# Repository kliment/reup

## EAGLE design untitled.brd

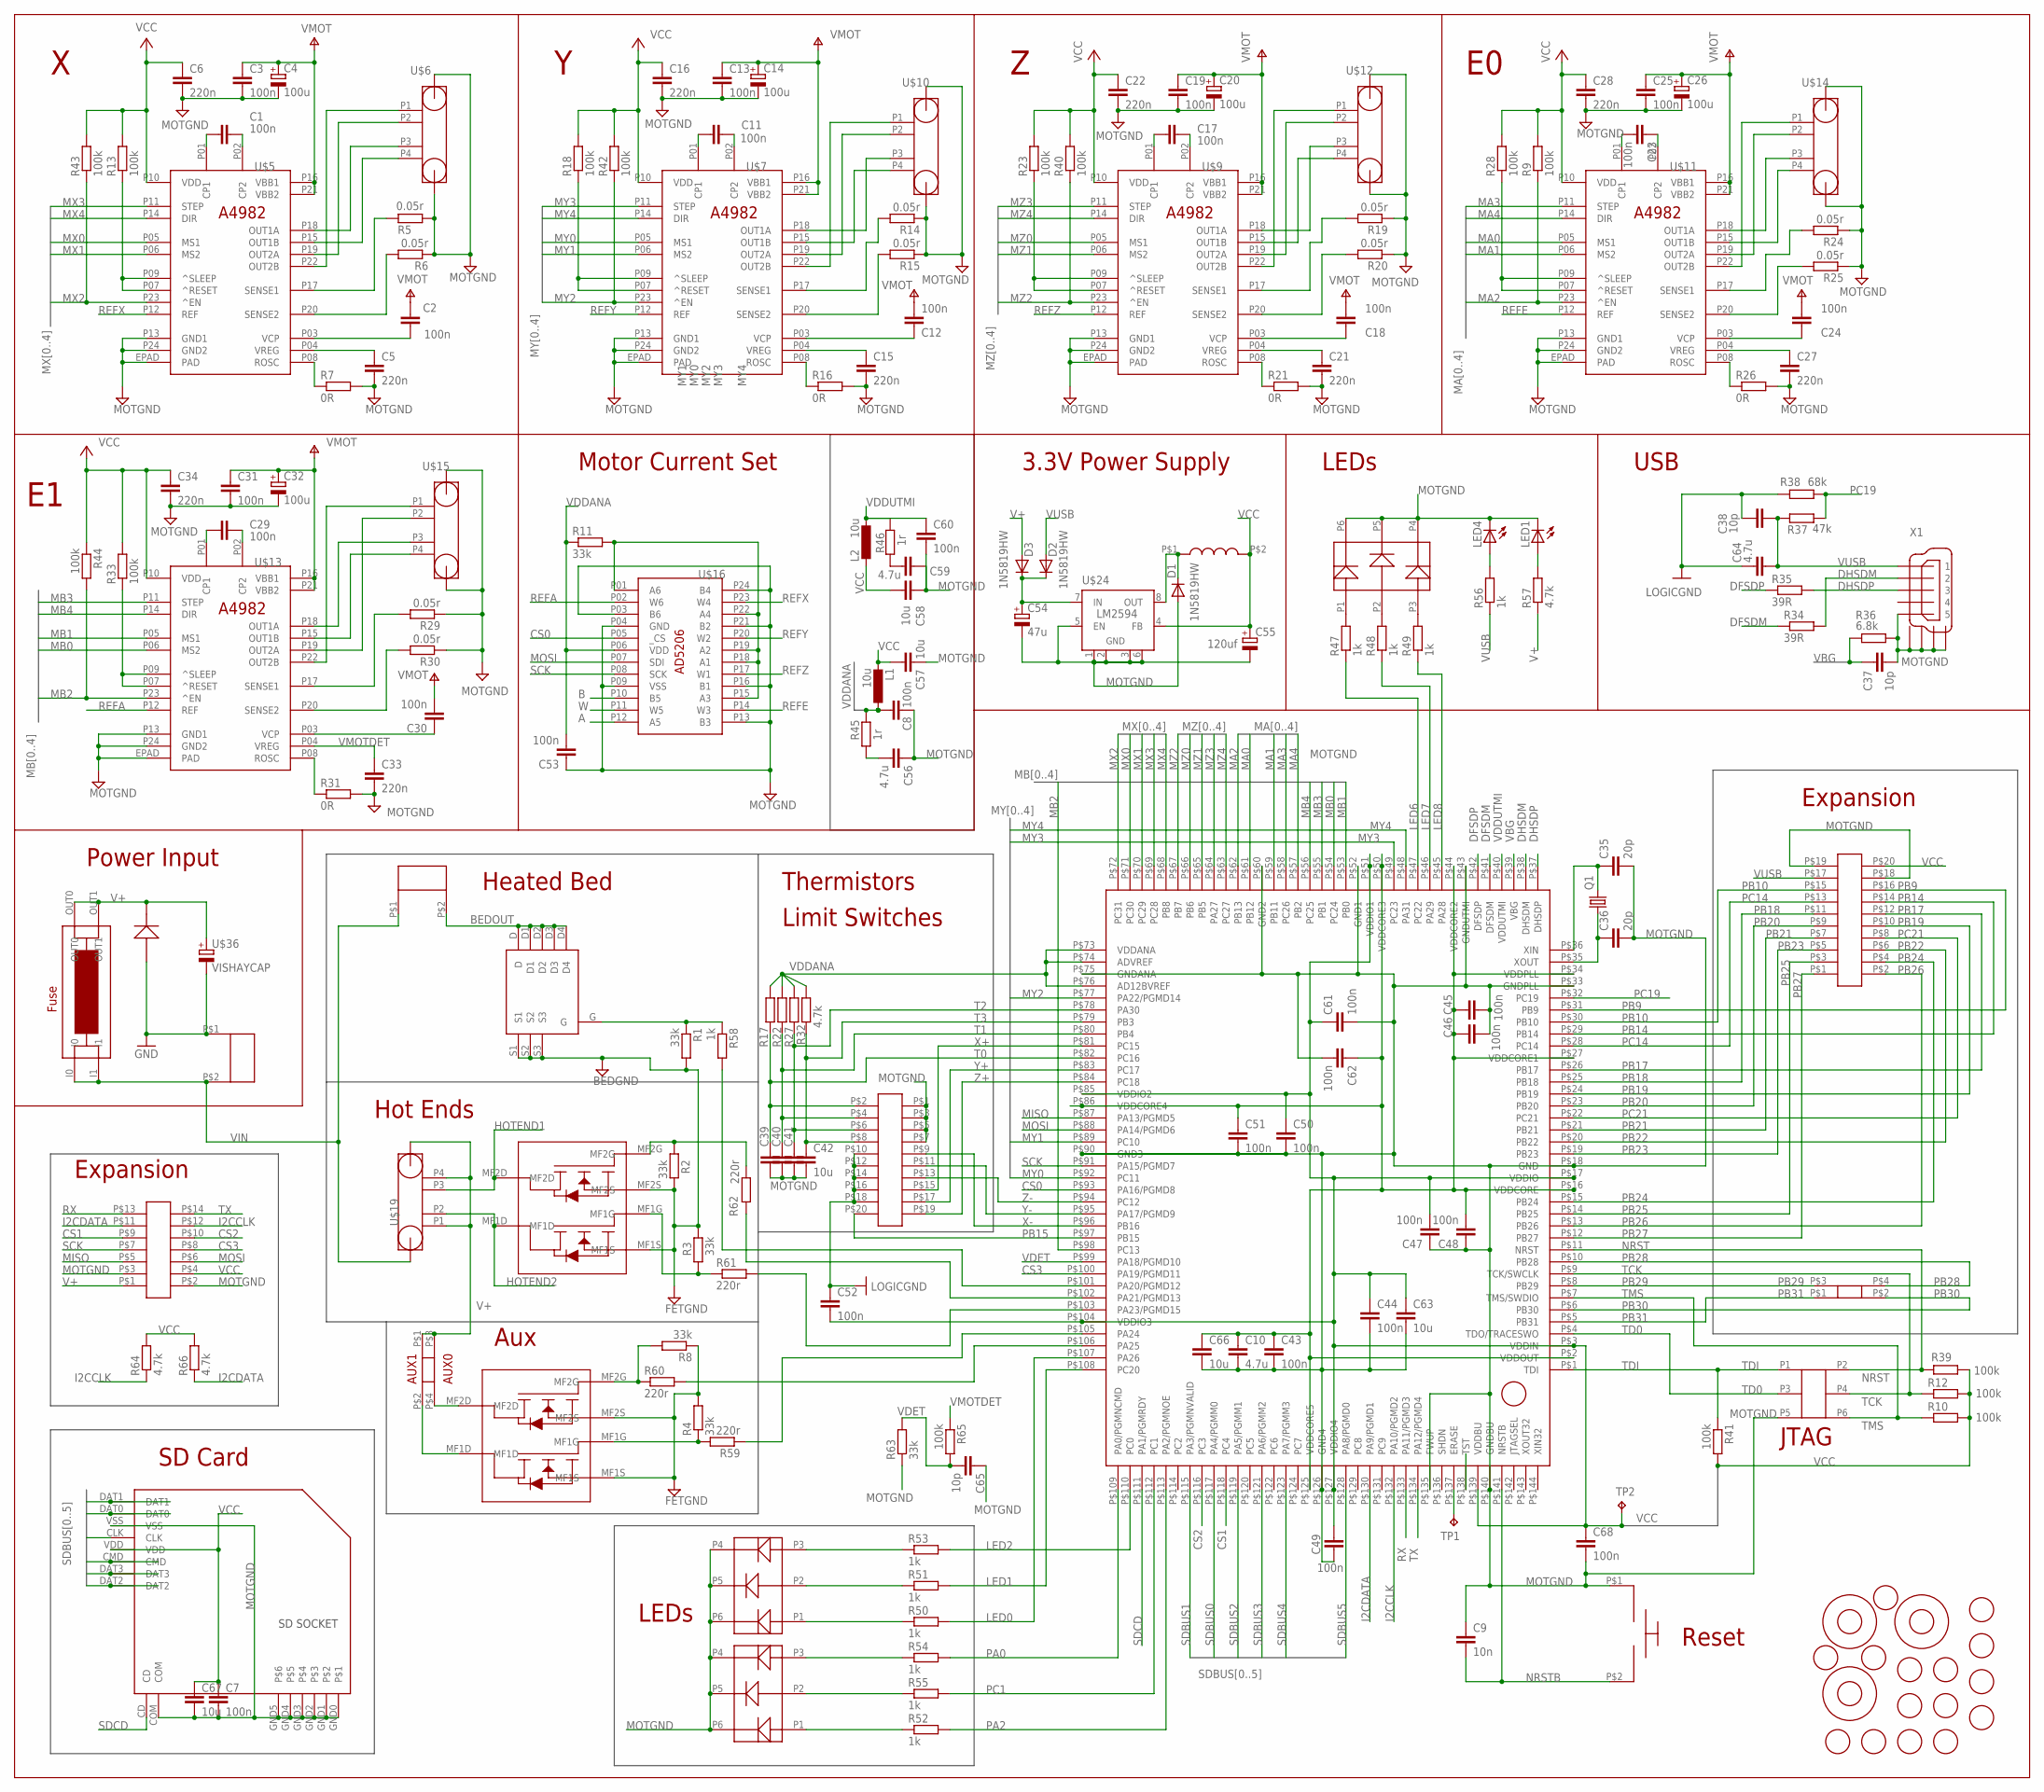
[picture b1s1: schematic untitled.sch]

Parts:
C1, C2, C3, C7, C8, C11, C12, C13, C17, C18, C19, C23, C24, C25, C29, C30, C31, C43, C44, C45, C46, C47, C48, C49, C50, C51, C52, C53, C60, C61, C62, C68: 100n; C0603K
C4, C14, C20, C26, C32: 100u; UD-6,3X7,7_NICHICON
C5, C6, C15, C16, C21, C22, C27, C28, C33, C34: 220n; C0603K
C9: 10n; C0603K
C10, C56, C59, C64: 4.7u; C0603K
C35, C36: 20p; C0603K
C37, C38, C65: 10p; C0603K
C39, C40, C41, C42, C57, C58, C63, C66, C67: 10u; C0603K
C54: 47u; D/7343-31R
C55: 120uf; 153CLV-0807
D1, D2, D3: 1N5819HW; SOD123
L1, L2: 10u; L2825P
LED1, LED4: LEDCHIPLED_0805; CHIPLED_0805
Q1: CSM-7X-DU
R1, R2, R3, R4, R8, R11, R63: 33k; R0603
R5, R6, R14, R15, R19, R20, R24, R25, R29, R30: 0.05r; R2512
R7, R16, R21, R26, R31: 0R; R0603
R9, R10, R12, R13, R18, R23, R28, R33, R39, R40, R41, R42, R43, R44, R65: 100k; R0603
R17, R22, R27, R32, R57, R64, R66: 4.7k; R0603
R34, R35: 39R; R0603
R36: 6.8k; R0603
R37: 47k; R0603
R38: 68k; R0603
R45, R46: 1r; R0603
R47, R48, R49, R50, R51, R52, R53, R54, R55, R56, R58: 1k; R0603
R59, R60, R61, R62: 220r; R0603
TP1, TP2: TPTP20R; TP20R
U$1, U$2: IPG20N04S4L-11; SUPERSO8
U$3, U$17: SMD.1X20; SMD0.1X20
U$4: IRFH6200; PQFNFET
U$5, U$7, U$9, U$11, U$13: A4982; ETSSOP24
U$6, U$10, U$12, U$14, U$15, U$19: 210-A-126-SMD; 210-A-126-SMD-4
U$8: SAM3U4E; LQFP144
U$16: AD5206; TSSOP24
U$18: SMD.1X6; SMD0.1X6
U$20, U$28: SMD.1; SMD0.1
U$21: 950-D-SMD-DS-2; 950-D-SMD-2
U$22: 974-D-SMD-2
U$23, U$29, U$30: GFUD; FIDUCIAL_G10
U$24: LM2594; SO08
U$25: SDCARD
U$26: FUSE; FUSEHOLDER
U$27: BUTTON
U$31: 100uH; INDUCTOR
U$32: FM4004; SMX
U$33, U$34, U$35: OMRONLED
U$36: VISHAYCAP; 153CLV-0810
U$37, U$38, U$39, U$40, U$41, U$42, U$44, U$45, U$46, U$47, U$48, U$49, U$50, U$51, U$52: LFUD; FIDUCIAL_L10
U$43: SMD.1X14; SMD0.1X14
X1: USBC

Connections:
A: U$16.P12 (A5)
B: U$16.P10 (B5)
BEDFET-G: R58.2, U$8.P$101 (PA20/PGMD12)
BEDOUT: U$4.D, U$4.D1, U$4.D2, U$4.D3, U$4.D4, U$21.P$2
CS0: U$8.P$93 (PA16/PGMD8), U$16.P05 (_CS)
CS1: U$8.P$118 (PC4), U$43.P$9
CS2: U$8.P$116 (PC3), U$43.P$10
CS3: U$8.P$100 (PA19/PGMD11), U$43.P$8
DFSDM: R34.1, U$8.P$41 (DFSDM)
DFSDP: R35.1, U$8.P$42 (DFSDP)
DHSDM: R34.2, U$8.P$38 (DHSDM), X1.2
DHSDP: R35.2, U$8.P$37 (DHSDP), X1.3
FET1-G: R60.2, U$8.P$106 (PA25)
FET2-G: R59.1, U$8.P$105 (PA24)
HE1-G: R62.2, U$8.P$102 (PA21/PGMD13)
HE2-G: R61.2, U$8.P$103 (PA23/PGMD15)
HOTEND1: U$2.MF2D, U$19.P3
HOTEND2: U$2.MF1D, U$19.P2
I2CCLK: R64.1, U$8.P$132 (PA10/PGMD2), U$43.P$12
I2CDATA: R66.1, U$8.P$130 (PA9/PGMD1), U$43.P$11
LED1: R47.1, U$8.P$47 (PC22)
LED2: R48.1, U$8.P$46 (PA29)
LED3: R49.1, U$8.P$45 (PA28)
LED4: R52.2, U$8.P$113 (PA2/PGMNOE)
LED5: R55.2, U$8.P$112 (PC1)
LED6: R54.2, U$8.P$109 (PA0/PGMNCMD)
LED7: R50.2, U$8.P$107 (PA26)
LED8: R51.2, U$8.P$108 (PC20)
LED9: R53.2, U$8.P$110 (PC0)
MA0: U$8.P$61 (PB12), U$11.P05 (MS1)
MA1: U$8.P$59 (PB11), U$11.P06 (MS2)
MA2: R9.1, U$8.P$62 (PB13), U$11.P23 (^EN)
MA3: U$8.P$58 (PC26), U$11.P11 (STEP)
MA4: U$8.P$57 (PB2), U$11.P14 (DIR)
MB0: U$8.P$54 (PC24), U$13.P06 (MS2)
MB1: U$8.P$53 (PB0), U$13.P05 (MS1)
MB2: R44.2, U$8.P$98 (PC13), U$13.P23 (^EN)
MB3: U$8.P$55 (PB1), U$13.P11 (STEP)
MB4: U$8.P$56 (PC25), U$13.P14 (DIR)
MISO: U$8.P$87 (PA13/PGMD5), U$43.P$5
MOSI: U$8.P$88 (PA14/PGMD6), U$16.P07 (SDI), U$43.P$6
MOTGND: C3.2, C4.-, C5.2, C6.2, C7.2, C8.2, C9.1, C10.2, C13.2, C14.-, C15.2, C16.2, C19.2, C20.-, C21.2, C22.2, C25.2, C26.-, C27.2, C28.2, C31.2, C32.-, C33.2, C34.2, C35.2, C36.2, C37.2, C38.2, C39.2, C40.2, C41.2, C42.2, C43.2, C44.2, C45.2, C46.1, C47.1, C48.1, C49.2, C50.2, C51.2, C52.1, C53.1, C54.-, C55.-, C56.1, C57.1, C58.1, C59.1, C60.2, C61.2, C62.2, C63.2, C64.1, C65.1, C66.2, C67.2, C68.2, D1.A, LED1.C, LED4.C, R1.2, R2.2, R3.2, R4.2, R5.1, R6.1, R7.2, R8.1, R14.1, R15.1, R16.2, R19.1, R20.1, R21.2, R24.1, R25.1, R26.2, R29.1, R30.1, R31.2, R36.2, R38.1, R63.1, U$1.MF1S, U$1.MF2S, U$2.MF1S, U$2.MF2S, U$3.P$18, U$3.P$19, U$4.S1, U$4.S2, U$4.S3, U$5.EPAD (PAD), U$5.P13 (GND1), U$5.P24 (GND2), U$6.GND0, U$6.GND1, U$7.EPAD (PAD), U$7.P13 (GND1), U$7.P24 (GND2), U$8.P$18 (GND), U$8.P$33 (GNDPLL), U$8.P$43 (GNDUTMI), U$8.P$52 (GND1), U$8.P$60 (GND2), U$8.P$75 (GNDANA), U$8.P$90 (GND3), U$8.P$126 (GND4), U$8.P$135 (FWUP), U$8.P$140 (GNDBU), U$9.EPAD (PAD), U$9.P13 (GND1), U$9.P24 (GND2), U$10.GND0, U$10.GND1, U$11.EPAD (PAD), U$11.P13 (GND1), U$11.P24 (GND2), U$12.GND0, U$12.GND1, U$13.EPAD (PAD), U$13.P13 (GND1), U$13.P24 (GND2), U$14.GND0, U$14.GND1, U$15.GND0, U$15.GND1, U$16.P03 (B6), U$16.P04 (GND), U$16.P09 (VSS), U$16.P13 (B3), U$16.P16 (B1), U$16.P21 (B2), U$16.P24 (B4), U$17.P$1, U$17.P$3, U$17.P$5, U$17.P$7, U$17.P$10, U$17.P$12, U$17.P$14, U$17.P$16, U$17.P$18, U$18.P5, U$22.P$1, U$24.1 (GND), U$24.2 (GND1), U$24.3 (GND2), U$24.5 (EN), U$24.6 (GND), U$25.COM, U$25.GND0, U$25.GND1, U$25.GND2, U$25.GND3, U$25.GND4, U$25.GND5, U$25.VSS, U$27.P$1, U$32.P$2, U$33.P4, U$33.P5, U$33.P6, U$34.P4, U$34.P5, U$34.P6, U$35.P4, U$35.P5, U$35.P6, U$36.-, U$43.P$2, U$43.P$3, X1.5, X1.M1, X1.M2, X1.M3, X1.M4
MX0: U$5.P05 (MS1), U$8.P$71 (PC30)
MX1: U$5.P06 (MS2), U$8.P$70 (PC29)
MX2: R43.1, U$5.P23 (^EN), U$8.P$72 (PC31)
MX3: U$5.P11 (STEP), U$8.P$69 (PC28)
MX4: U$5.P14 (DIR), U$8.P$68 (PB8)
MY0: U$7.P05 (MS1), U$8.P$92 (PC11)
MY1: U$7.P06 (MS2), U$8.P$89 (PC10)
MY2: R42.1, U$7.P23 (^EN), U$8.P$77 (PA22/PGMD14)
MY3: U$7.P11 (STEP), U$8.P$49 (PC23)
MY4: U$7.P14 (DIR), U$8.P$48 (PA31)
MZ0: U$8.P$66 (PB6), U$9.P05 (MS1)
MZ1: U$8.P$65 (PB5), U$9.P06 (MS2)
MZ2: R40.1, U$8.P$67 (PB7), U$9.P23 (^EN)
MZ3: U$8.P$64 (PA27), U$9.P11 (STEP)
MZ4: U$8.P$63 (PC27), U$9.P14 (DIR)
unnamed: R11.2, U$16.P01 (A6), U$16.P15 (A3), U$16.P18 (A1), U$16.P19 (A2), U$16.P22 (A4)
unnamed: R5.2, U$5.P17 (SENSE1)
unnamed: R6.2, U$5.P20 (SENSE2)
unnamed: C1.2, U$5.P01 (CP1)
unnamed: C1.1, U$5.P02 (CP2)
unnamed: C2.1, U$5.P03 (VCP)
unnamed: R13.1, U$5.P07 (^RESET), U$5.P09 (^SLEEP)
unnamed: TP1.TP, U$8.P$137 (ERASE)
unnamed: R15.2, U$7.P20 (SENSE2)
unnamed: C5.1, U$5.P04 (VREG)
unnamed: R7.1, U$5.P08 (ROSC)
unnamed: U$5.P15 (OUT1B), U$6.P4
unnamed: U$5.P19 (OUT2A), U$6.P2
unnamed: C11.2, U$7.P01 (CP1)
unnamed: U$5.P22 (OUT2B), U$6.P1
unnamed: R1.1, R58.1, U$4.G
unnamed: C23.2, U$11.P01 (CP1)
unnamed: R29.2, U$13.P17 (SENSE1)
unnamed: R30.2, U$13.P20 (SENSE2)
unnamed: C23.1, U$11.P02 (CP2)
unnamed: C29.2, U$13.P01 (CP1)
unnamed: R4.1, R59.2, U$1.MF1G
unnamed: C29.1, U$13.P02 (CP2)
unnamed: C24.1, U$11.P03 (VCP)
unnamed: R28.1, U$11.P07 (^RESET), U$11.P09 (^SLEEP)
unnamed: C17.2, U$9.P01 (CP1)
unnamed: C27.1, U$11.P04 (VREG)
unnamed: C18.1, U$9.P03 (VCP)
unnamed: R26.1, U$11.P08 (ROSC)
unnamed: R21.1, U$9.P08 (ROSC)
unnamed: U$9.P19 (OUT2A), U$12.P2
unnamed: U$9.P15 (OUT1B), U$12.P4
unnamed: U$11.P19 (OUT2A), U$14.P2
unnamed: U$11.P15 (OUT1B), U$14.P4
unnamed: R8.2, R60.1, U$1.MF2G
unnamed: R3.1, R61.1, U$2.MF1G
unnamed: R33.1, U$13.P07 (^RESET), U$13.P09 (^SLEEP)
unnamed: U$5.P18 (OUT1A), U$6.P3
unnamed: U$13.P15 (OUT1B), U$15.P4
unnamed: R14.2, U$7.P17 (SENSE1)
unnamed: C30.1, U$13.P03 (VCP)
unnamed: C11.1, U$7.P02 (CP2)
unnamed: C12.1, U$7.P03 (VCP)
unnamed: R2.1, R62.1, U$2.MF2G
unnamed: C15.1, U$7.P04 (VREG)
unnamed: R16.1, U$7.P08 (ROSC)
unnamed: U$1.MF2D, U$20.P$4
unnamed: U$11.P18 (OUT1A), U$14.P3
unnamed: U$7.P19 (OUT2A), U$10.P2
unnamed: R31.1, U$13.P08 (ROSC)
unnamed: R19.2, U$9.P17 (SENSE1)
unnamed: U$1.MF1D, U$20.P$2
unnamed: U$7.P15 (OUT1B), U$10.P4
unnamed: U$13.P19 (OUT2A), U$15.P2
unnamed: R18.1, U$7.P07 (^RESET), U$7.P09 (^SLEEP)
unnamed: C17.1, U$9.P02 (CP2)
unnamed: U$13.P22 (OUT2B), U$15.P1
unnamed: U$7.P22 (OUT2B), U$10.P1
unnamed: U$9.P18 (OUT1A), U$12.P3
unnamed: U$9.P22 (OUT2B), U$12.P1
unnamed: U$7.P18 (OUT1A), U$10.P3
unnamed: U$13.P18 (OUT1A), U$15.P3
unnamed: R20.2, U$9.P20 (SENSE2)
unnamed: R23.1, U$9.P07 (^RESET), U$9.P09 (^SLEEP)
unnamed: R24.2, U$11.P17 (SENSE1)
unnamed: R25.2, U$11.P20 (SENSE2)
unnamed: U$11.P22 (OUT2B), U$14.P1
unnamed: D1.C, U$24.8 (OUT), U$31.P$1
unnamed: C54.+, D2.C, D3.C, U$24.7 (IN)
unnamed: C56.2, R45.1
unnamed: C59.2, R46.1
unnamed: R48.2, U$33.P2
unnamed: R50.1, U$34.P1
unnamed: R51.1, U$34.P2
unnamed: R53.1, U$34.P3
unnamed: R55.1, U$35.P2
unnamed: R54.1, U$35.P3
unnamed: R52.1, U$35.P1
unnamed: R49.2, U$33.P3
unnamed: R47.2, U$33.P1
unnamed: LED4.A, R56.2
unnamed: LED1.A, R57.2
NRST: R39.2, U$8.P$11 (NRST), U$18.P2
NRSTB: C9.2, U$8.P$141 (NRSTB), U$27.P$2
PB9: U$3.P$16, U$8.P$31 (PB9)
PB10: U$3.P$15, U$8.P$30 (PB10)
PB14: U$3.P$14, U$8.P$29 (PB14)
PB15: U$8.P$97 (PB15), U$17.P$20
PB17: U$3.P$12, U$8.P$26 (PB17)
PB18: U$3.P$11, U$8.P$25 (PB18)
PB19: U$3.P$10, U$8.P$24 (PB19)
PB20: U$3.P$9, U$8.P$23 (PB20)
PB21: U$3.P$7, U$8.P$21 (PB21)
PB22: U$3.P$6, U$8.P$20 (PB22)
PB23: U$3.P$5, U$8.P$19 (PB23)
PB24: U$3.P$4, U$8.P$15 (PB24)
PB25: U$3.P$3, U$8.P$14 (PB25)
PB26: U$3.P$2, U$8.P$13 (PB26)
PB27: U$3.P$1, U$8.P$12 (PB27)
PB28: U$8.P$10 (PB28), U$28.P$4
PB29: U$8.P$8 (PB29), U$28.P$3
PB30: U$8.P$6 (PB30), U$28.P$2
PB31: U$8.P$5 (PB31), U$28.P$1
PC14: U$3.P$13, U$8.P$28 (PC14)
PC21: U$3.P$8, U$8.P$22 (PC21)
REFA: U$13.P12 (REF), U$16.P02 (W6)
REFE: U$11.P12 (REF), U$16.P14 (W3)
REFX: U$5.P12 (REF), U$16.P23 (W4)
REFY: U$7.P12 (REF), U$16.P20 (W2)
REFZ: U$9.P12 (REF), U$16.P17 (W1)
RX: U$8.P$133 (PA11/PGMD3), U$43.P$13
SCK: U$8.P$91 (PA15/PGMD7), U$16.P08 (SCK), U$43.P$7
SDBUS0: U$8.P$117 (PA4/PGMM0), U$25.CMD
SDBUS1: U$8.P$115 (PA3/PGMNVALID), U$25.CLK
SDBUS2: U$8.P$119 (PA5/PGMM1), U$25.DAT0
SDBUS3: U$8.P$121 (PA6/PGMM2), U$25.DAT1
SDBUS4: U$8.P$123 (PA7/PGMM3), U$25.DAT2
SDBUS5: U$8.P$128 (PA8/PGMD0), U$25.DAT3
SDCD: U$8.P$111 (PA1/PGMRDY), U$25.CD
T0: C39.1, R17.1, U$8.P$82 (PC16), U$17.P$2
T1: C40.1, R22.1, U$8.P$80 (PB4), U$17.P$4
T2: C41.1, R27.1, U$8.P$78 (PA30), U$17.P$6
T3: C42.1, R32.1, U$8.P$79 (PB3), U$17.P$8
TCK: R12.1, U$8.P$9 (TCK/SWCLK), U$18.P4
TD0: U$8.P$4 (TDO/TRACESWO), U$18.P3
TDI: R41.1, U$8.P$1 (TDI), U$18.P1
TMS: R10.1, U$8.P$7 (TMS/SWDIO), U$18.P6
TST: U$8.P$138 (TST)
TX: U$8.P$134 (PA12/PGMD4), U$43.P$14
USBDET: R37.1, R38.2, U$8.P$32 (PC19)
V+: C2.2, C3.1, C4.+, C12.2, C13.1, C14.+, C18.2, C19.1, C20.+, C24.2, C25.1, C26.+, C30.2, C31.1, C32.+, D3.A, R57.1, U$5.P16 (VBB1), U$5.P21 (VBB2), U$7.P16 (VBB1), U$7.P21 (VBB2), U$9.P16 (VBB1), U$9.P21 (VBB2), U$11.P16 (VBB1), U$11.P21 (VBB2), U$13.P16 (VBB1), U$13.P21 (VBB2), U$19.GND1, U$19.P1, U$19.P4, U$20.P$1, U$20.P$3, U$26.OUT0, U$26.OUT1, U$32.P$1, U$36.+, U$43.P$1
VBG: C37.1, R36.1, U$8.P$39 (VBG)
VCC: C6.1, C7.1, C16.1, C22.1, C28.1, C34.1, C44.1, C47.2, C49.1, C50.1, C52.2, C55.+, C57.2, C58.2, C61.1, C63.1, C67.1, C68.1, L1.2, L2.1, R9.2, R10.2, R12.2, R13.2, R18.2, R23.2, R28.2, R33.2, R39.1, R40.2, R41.2, R42.2, R43.2, R44.1, R64.2, R66.2, TP2.TP, U$3.P$20, U$5.P10 (VDD), U$7.P10 (VDD), U$8.P$3 (VDDIN), U$8.P$17 (VDDIO), U$8.P$51 (VDDIO1), U$8.P$85 (VDDIO2), U$8.P$104 (VDDIO3), U$8.P$127 (VDDIO4), U$8.P$139 (VDDBU), U$9.P10 (VDD), U$11.P10 (VDD), U$13.P10 (VDD), U$24.4 (FB), U$25.VDD, U$31.P$2, U$43.P$4
VCORE: C10.1, C43.1, C45.1, C46.2, C48.2, C51.1, C62.1, C66.1, U$8.P$2 (VDDOUT), U$8.P$16 (VDDCORE), U$8.P$27 (VDDCORE1), U$8.P$34 (VDDPLL), U$8.P$44 (VDDCORE2), U$8.P$50 (VDDCORE3), U$8.P$86 (VDDCORE4), U$8.P$125 (VDDCORE5)
VDDANA: C8.1, C53.2, L1.1, R11.1, R17.2, R22.2, R27.2, R32.2, R45.2, U$8.P$73 (VDDANA), U$8.P$74 (ADVREF), U$8.P$76 (AD12BVREF), U$16.P06 (VDD)
VDDUTMI: C60.1, L2.2, R46.2, U$8.P$40 (VDDUTMI)
VDET: C65.2, R63.2, R65.2, U$8.P$99 (PA18/PGMD10)
VIN: U$19.GND0, U$21.P$1, U$22.P$2, U$26.I0, U$26.I1
VMOTDET: C33.1, R65.1, U$13.P04 (VREG)
VREG: C21.1, U$9.P04 (VREG)
VUSB: C38.1, C64.2, D2.A, R37.2, R56.1, U$3.P$17, X1.1
W: U$16.P11 (W5)
X+: U$8.P$81 (PC15), U$17.P$15
X-: U$8.P$96 (PB16), U$17.P$9
XTAL1: C35.1, Q1.2, U$8.P$36 (XIN)
XTAL2: C36.1, Q1.1, U$8.P$35 (XOUT)
Y+: U$8.P$83 (PC17), U$17.P$17
Y-: U$8.P$95 (PA17/PGMD9), U$17.P$11
Z+: U$8.P$84 (PC18), U$17.P$19
Z-: U$8.P$94 (PC12), U$17.P$13

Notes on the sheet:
SD SOCKET
Motor Current Set
3.3V Power Supply
USB
Power Input
Fuse
AUX0
AUX1
SD Card
Thermistors
Limit Switches
Heated Bed
Hot Ends
Aux
Reset
JTAG
Expansion
LEDs

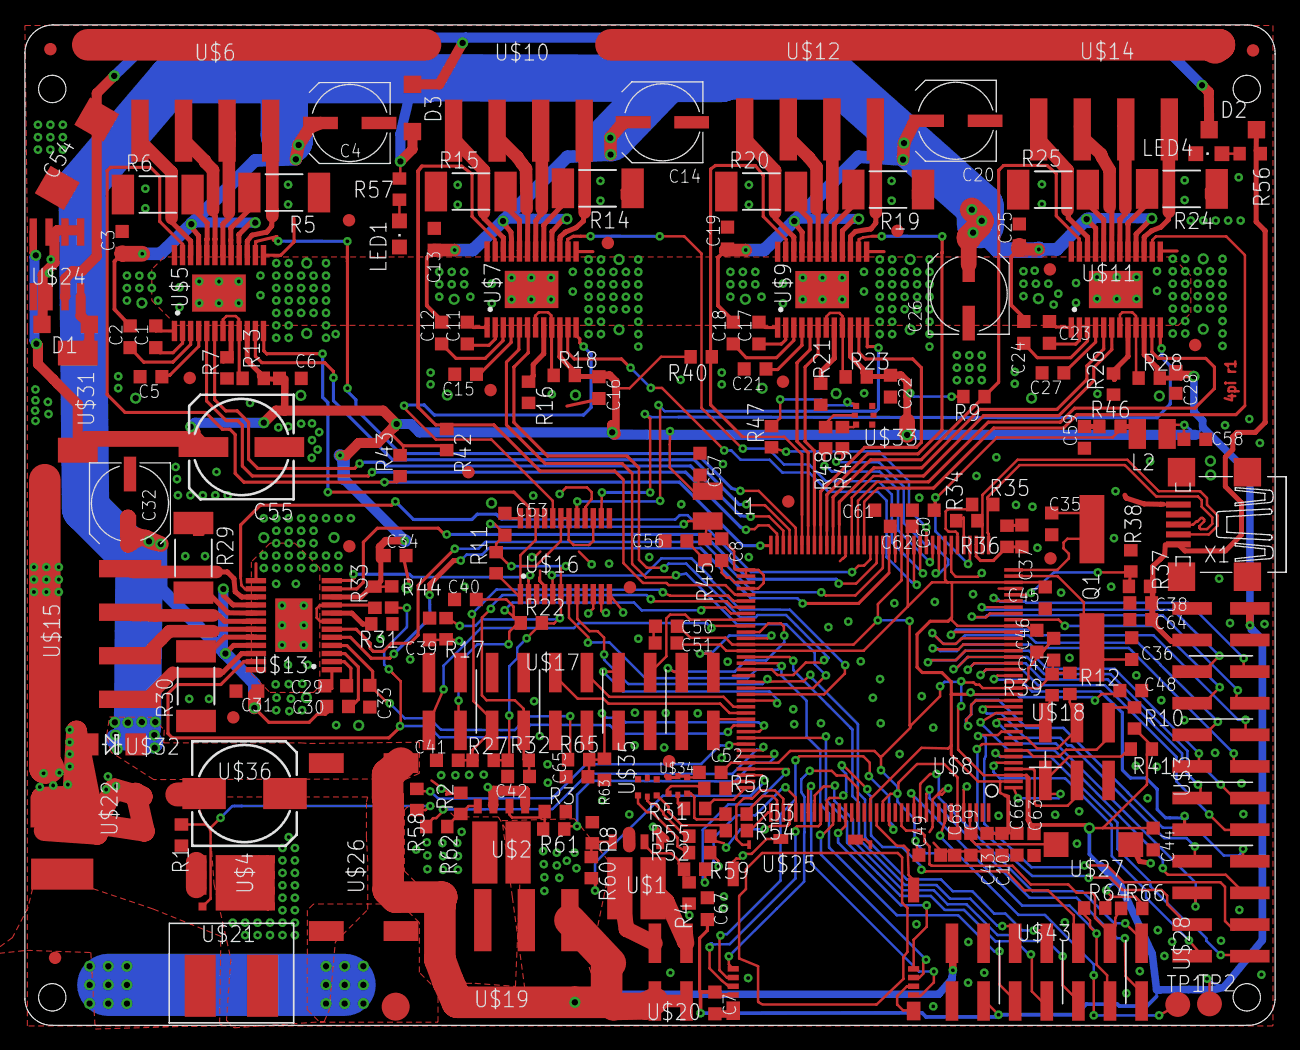
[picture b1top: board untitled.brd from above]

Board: 2 copper layers, 100.5 x 80.4 mm, 197 parts (0 on the bottom side), 203 nets.

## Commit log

2011-10-06 Added initial 5 axis board layout
2011-10-26 Added footprint for Weco SMD screw terminal.
2011-10-26 Improve thermal layout for stepper modules. Add sam3u chip and initial connections. Make microstepping software controlled. Increase +12v trace thickness for motors.
2011-10-27 Copy stepper driver module, move cap on 4th driver, add MOTV+ routing
2011-10-27 Add pours, wire USB
2011-10-30 Change package on processor
2011-11-02 Added potentiometer. Routed most of the board. Fixed most DRC violations - board can be done with 8mil process
2011-11-02 Add thermistor/endstop headers (not yet routed). Fix DRC violations.
2011-11-02 Add several connectors. Move FETs around to make space.
2011-11-04 Add SD, expansion header, thermistor passives, power connector, bed connector. Reroute USB to be high speed compatible. Add extra FET channel. Move hotends to a dual FET chip.
2011-11-06 Route endstop and thermistor connector. Switch to different bed FET. Route SPI to pot chip. Add reset button and fuse.
2011-11-07 Expansion headers routed. Started schematic cleanup. Added half of decoupling/filtering circuits. FET thermals and power routing done.
2011-11-07 Added some more power filtering. Cleaned up some reverse side traces.
2011-11-08 Added most of the buck converter circuitry (except caps and possibly filter inductor on output). Added more decoupling and rerouted analog inputs (now at left of header). Freed up space on corner of 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
2011-11-08 Added 3.3V pre and post converter caps. Routed logic power circuitry.
2011-11-09 Added power filtering for the sam3u's utmi and analog supplies. Added component values for all decoupling caps.
2011-11-10 Added protection diode, 3 software controlled RGB LEDs, and indicator LEDs for USB and 12V power.
2011-11-10 Schematic cleanup
2011-11-10 Straighten some paths
2011-11-10 Add part number to diodes
2011-11-10 Add input capacitor and silkscreen markings.
2011-11-11 Add filter cap on USB power input
2011-11-11 Added flash erase pads, silkscreen markings and exported image file
2011-11-11 Move fuse holder a bit to ensure solder mask bridge between temp header and +12V
2011-11-14 Change solder paste profiles for components with large ground pads.
2011-12-06 Fix footprint of 0.1" headers. Improve ground current paths. Remove thermals on high current paths.
2011-12-07 Make mountinh holes M2 and add clearance
2011-12-09 Reduce number of drill sizes to 3 for cheaper manufacture.
2011-12-19 Rotate FET, make space for endstop signal filtering.
2011-12-20 Align 0.1" headers with each other. More space around USB data lines. More spacing around some passives. Better ground path from the drivers to the power connector. Fix silkscreen label positioning. 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
2011-12-26 Minor positioning tweaks
2011-12-29 Fix wrong footprint on SD socket. Reroute affected area. Pin changes for the RGB LEDs and SD card detect.
2011-12-29 Add current limiting series resistors to FETs. Remove all exposed traces/vias from the SD no pattern area. Switch potentiometer supply and reference to filtered power.
2011-12-29 Switch thermistor reference to filtered power supply.
2011-12-30 Add pin mapping. Minor schematic cleanup.
2011-12-30 Add bed heater pin
2012-01-01 Minor schematic and board cleanup
2012-01-05 Reroute 3 analog pins to endstop headers (causes changes in pin mappings). Add voltage divider for VMOT detection. Reroute the SD socket to respect keepout area. Fix trace angles. Major schematic cle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
2012-01-05 Regenerate board image.
2012-01-06 Move output capacitor closer to inductor on vreg. Move power input header north to make more space for bed connector. Move filter cap on power input closer to fuse.
2012-01-06 Update board image.
2012-01-07 Move USB F resistors closer to device pins. Minor optimization of USB path.
2012-01-07 Match USB trace length to within 0.12 mm (6mil)
2012-01-07 Updated board image to reflect changed USB routing
2012-01-08 Add extra filter cap to vcore. Add filter cap to VMOT detect.
2012-01-10 Add i2c pullups. Update silkscreen. Update board image.
2012-01-26 Add pullup resistors to SD data lines. Add extra decoupling to SD power. Regenerate board image.
2012-01-29 Update board image
2012-02-08 Fix a few library footprints to have correct orientation. Enlarge pads on bed MOSFET.
2012-02-14 Fix DRC errors according to stricter rules. Slightly extended board dimensions to ensure floating anchors are solidly attached.
2012-03-04 Add fiducial markers to board
2012-03-15 Update pinmap Change input capacitor package Improve E0 heatsinking Fix bed connector package
2012-03-15 Add BOM with sources
2012-03-16 Updated board image
2012-05-20 Clean up schematic somewhat. Update footprint for USB connector and 2x7 header. Move large decoupling cap for card power. Move silkscreen texts so they are off pads. Add silkscreen below USB connecto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
2012-07-01 Update library to have component names.
2012-09-25 Improved readability of schematic.
2012-09-25 Added pdf schematic
2012-09-25 Changed LED signal names to match pinmap.txt
2013-01-29 Added BOM table that was used to order parts for production
2013-01-29 Added further useful parts to lbr
